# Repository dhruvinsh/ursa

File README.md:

# Ursa

This is a split keyboard with 34~36 keys only.

# Render

Current status of the Render looks like as below:

## Credits

Kailh Socket 3D Model was obtained from [_QMK_](https://github.com/qmk). All credits go to them. The exact file can be found [here](https://github.com/qmk/qmk_hardware/blob/master/components/kailh_socket_mx.stp).

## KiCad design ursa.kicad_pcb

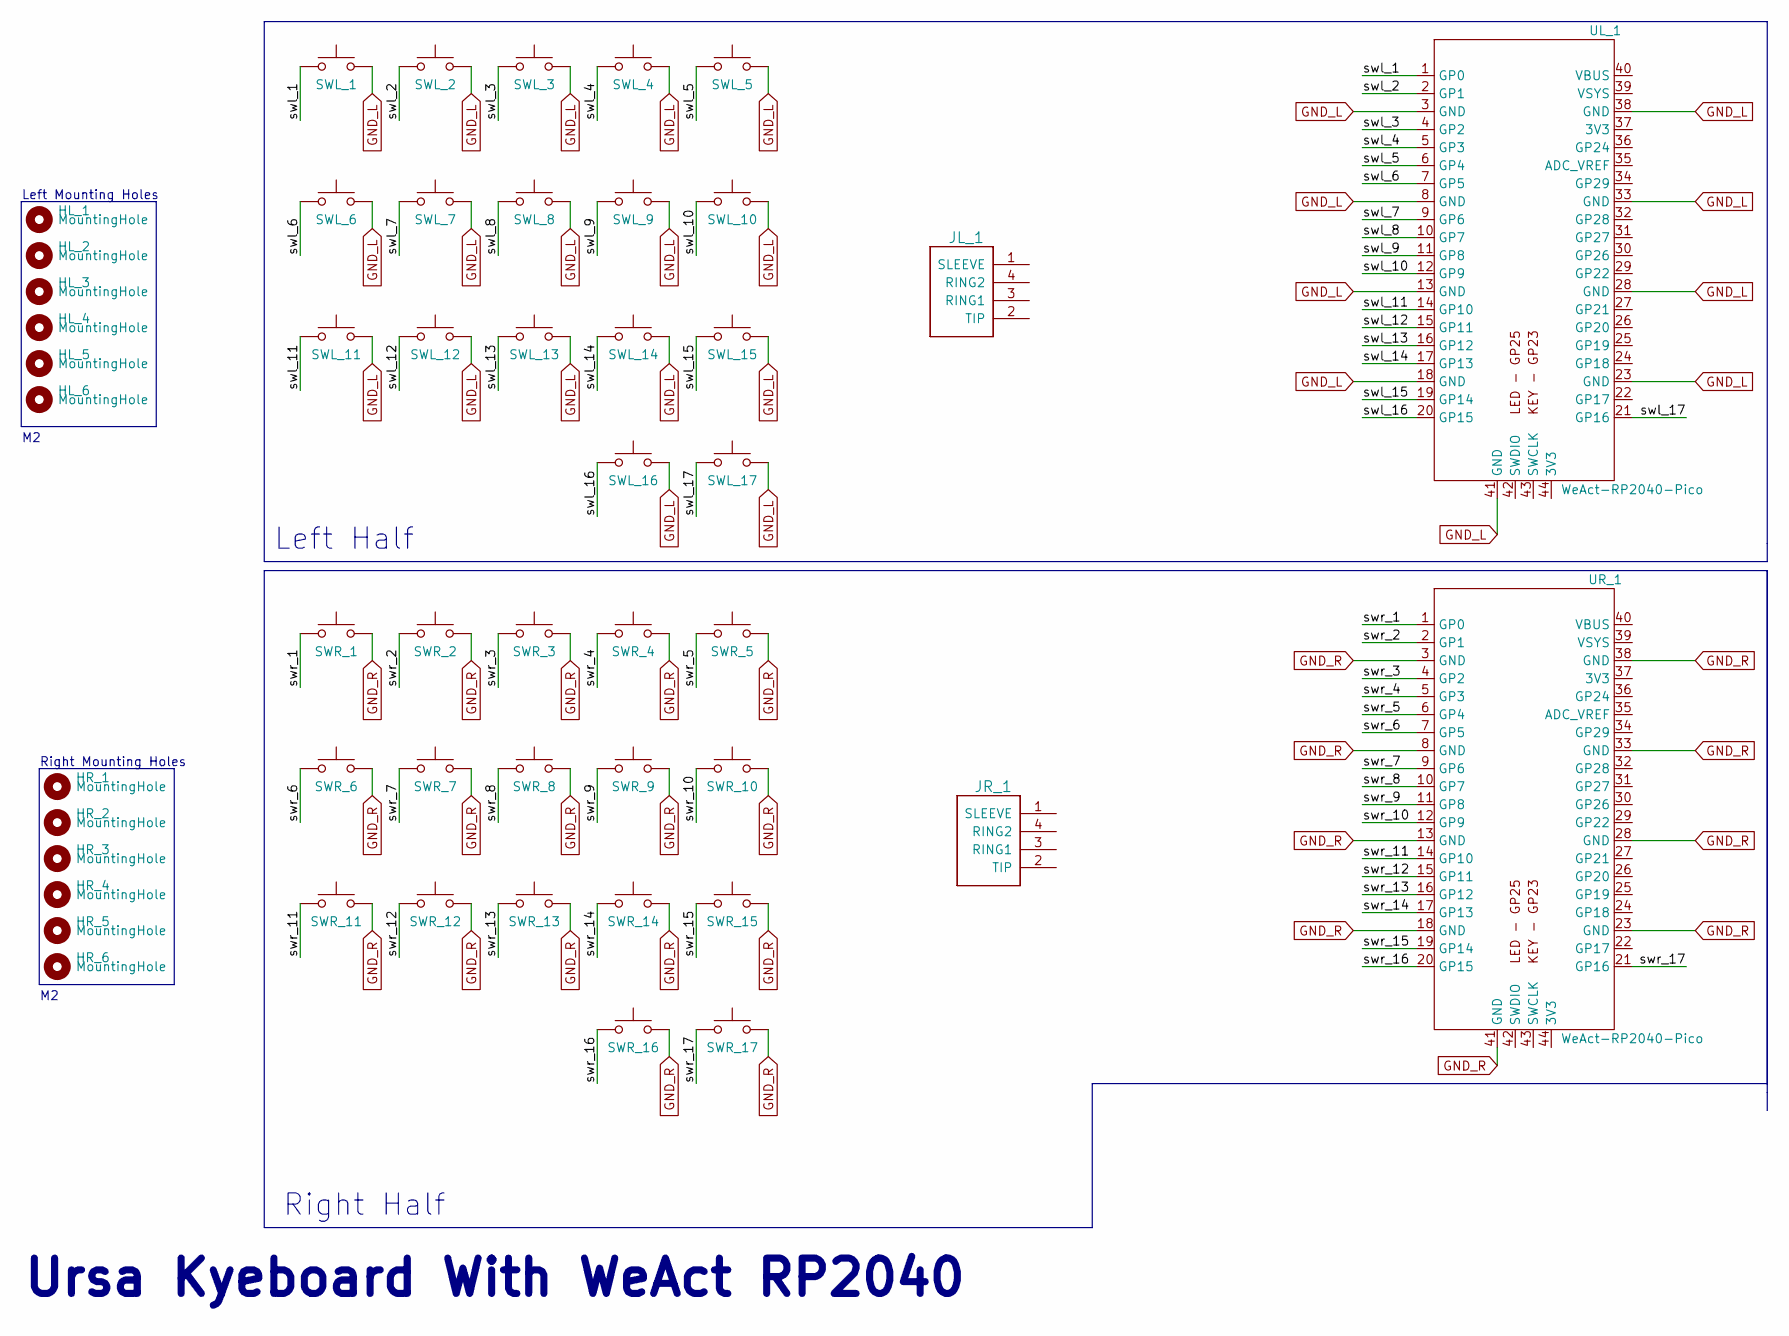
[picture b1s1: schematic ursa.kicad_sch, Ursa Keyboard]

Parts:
HL_1, HL_2, HL_3, HL_4, HL_5, HL_6: MountingHole; MountingHole_2.2mm_M2
HR_1, HR_2, HR_3, HR_4, HR_5, HR_6: MountingHole; MountingHole_2.2mm_M2
JL_1: TRRS; TRRS-PJ-320A
JR_1: TRRS; TRRS-PJ-320A
SWL_1, SWL_2, SWL_3, SWL_4, SWL_5, SWL_6, SWL_7, SWL_8, SWL_9, SWL_10, SWL_11, SWL_12, SWL_13, SWL_14, SWL_15, SWL_16, SWL_17: SW_Push; Kailh_socket_MX_optional
SWR_1, SWR_2, SWR_3, SWR_4, SWR_5, SWR_6, SWR_7, SWR_8, SWR_9, SWR_10, SWR_11, SWR_12, SWR_13, SWR_14, SWR_15, SWR_16, SWR_17: SW_Push; Kailh_socket_MX_optional
UL_1: WeAct-RP2040-Pico
UR_1: WeAct-RP2040-Pico

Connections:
/swl_1: SWL_1.1, UL_1.1 (GP0)
/swl_2: SWL_2.1, UL_1.2 (GP1)
/swl_3: SWL_3.1, UL_1.4 (GP2)
/swl_4: SWL_4.1, UL_1.5 (GP3)
/swl_5: SWL_5.1, UL_1.6 (GP4)
/swl_6: SWL_6.1, UL_1.7 (GP5)
/swl_7: SWL_7.1, UL_1.9 (GP6)
/swl_8: SWL_8.1, UL_1.10 (GP7)
/swl_9: SWL_9.1, UL_1.11 (GP8)
/swl_10: SWL_10.1, UL_1.12 (GP9)
/swl_11: SWL_11.1, UL_1.14 (GP10)
/swl_12: SWL_12.1, UL_1.15 (GP11)
/swl_13: SWL_13.1, UL_1.16 (GP12)
/swl_14: SWL_14.1, UL_1.17 (GP13)
/swl_15: SWL_15.1, UL_1.19 (GP14)
/swl_16: SWL_16.1, UL_1.20 (GP15)
/swl_17: SWL_17.1, UL_1.21 (GP16)
/swr_1: SWR_1.1, UR_1.1 (GP0)
/swr_2: SWR_2.1, UR_1.2 (GP1)
/swr_3: SWR_3.1, UR_1.4 (GP2)
/swr_4: SWR_4.1, UR_1.5 (GP3)
/swr_5: SWR_5.1, UR_1.6 (GP4)
/swr_6: SWR_6.1, UR_1.7 (GP5)
/swr_7: SWR_7.1, UR_1.9 (GP6)
/swr_8: SWR_8.1, UR_1.10 (GP7)
/swr_9: SWR_9.1, UR_1.11 (GP8)
/swr_10: SWR_10.1, UR_1.12 (GP9)
/swr_11: SWR_11.1, UR_1.14 (GP10)
/swr_12: SWR_12.1, UR_1.15 (GP11)
/swr_13: SWR_13.1, UR_1.16 (GP12)
/swr_14: SWR_14.1, UR_1.17 (GP13)
/swr_15: SWR_15.1, UR_1.19 (GP14)
/swr_16: SWR_16.1, UR_1.20 (GP15)
/swr_17: SWR_17.1, UR_1.21 (GP16)
GND_L: SWL_1.2, SWL_2.2, SWL_3.2, SWL_4.2, SWL_5.2, SWL_6.2, SWL_7.2, SWL_8.2, SWL_9.2, SWL_10.2, SWL_11.2, SWL_12.2, SWL_13.2, SWL_14.2, SWL_15.2, SWL_16.2, SWL_17.2, UL_1.3 (GND), UL_1.8 (GND), UL_1.13 (GND), UL_1.18 (GND), UL_1.23 (GND), UL_1.28 (GND), UL_1.33 (GND), UL_1.38 (GND), UL_1.41 (GND)
GND_R: SWR_1.2, SWR_2.2, SWR_3.2, SWR_4.2, SWR_5.2, SWR_6.2, SWR_7.2, SWR_8.2, SWR_9.2, SWR_10.2, SWR_11.2, SWR_12.2, SWR_13.2, SWR_14.2, SWR_15.2, SWR_16.2, SWR_17.2, UR_1.3 (GND), UR_1.8 (GND), UR_1.13 (GND), UR_1.18 (GND), UR_1.23 (GND), UR_1.28 (GND), UR_1.33 (GND), UR_1.38 (GND), UR_1.41 (GND)

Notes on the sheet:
Right Half
Ursa Kyeboard With WeAct RP2040
Right Mounting Holes
Left Half
Left Mounting Holes

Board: 2 copper layers, 50 parts (0 on the bottom side), 36 nets, no tracks yet.

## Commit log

2022-12-07 gitignore is added
2022-12-07 Adding kicad_prl files back
2022-12-07 Proper 3D model with switches and hotswap module
2022-12-08 trrs symbol added
2022-12-08 better wiring and through hole added
2022-12-08 no more git submodules
2022-12-08 Worked on layout
    * solder mask added
    * some lines added (not 100% sure what is called) to break the two
    * through-hole adjusted
    * still need to work on design
2022-12-09 Right side layout adjustment
    * now render shows split PCB, fixed an issue where the cut edge weren't
    set properly.
    * render images added
    * left side PCB adjusted little bit! Gave smoother edge on the right
    most parts but the TRRS and RP2040 side edge are still right angle.
    Still deciding what to do.
2022-12-09 README updated
2022-12-12 Some Zone.Identifier removed
